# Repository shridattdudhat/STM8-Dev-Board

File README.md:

# STM8-Dev-Board
STM8-Dev-Board with SoC STM8S003F3P6

Ki-CAD Project, to buy this connect me on electroShri@gmail.com

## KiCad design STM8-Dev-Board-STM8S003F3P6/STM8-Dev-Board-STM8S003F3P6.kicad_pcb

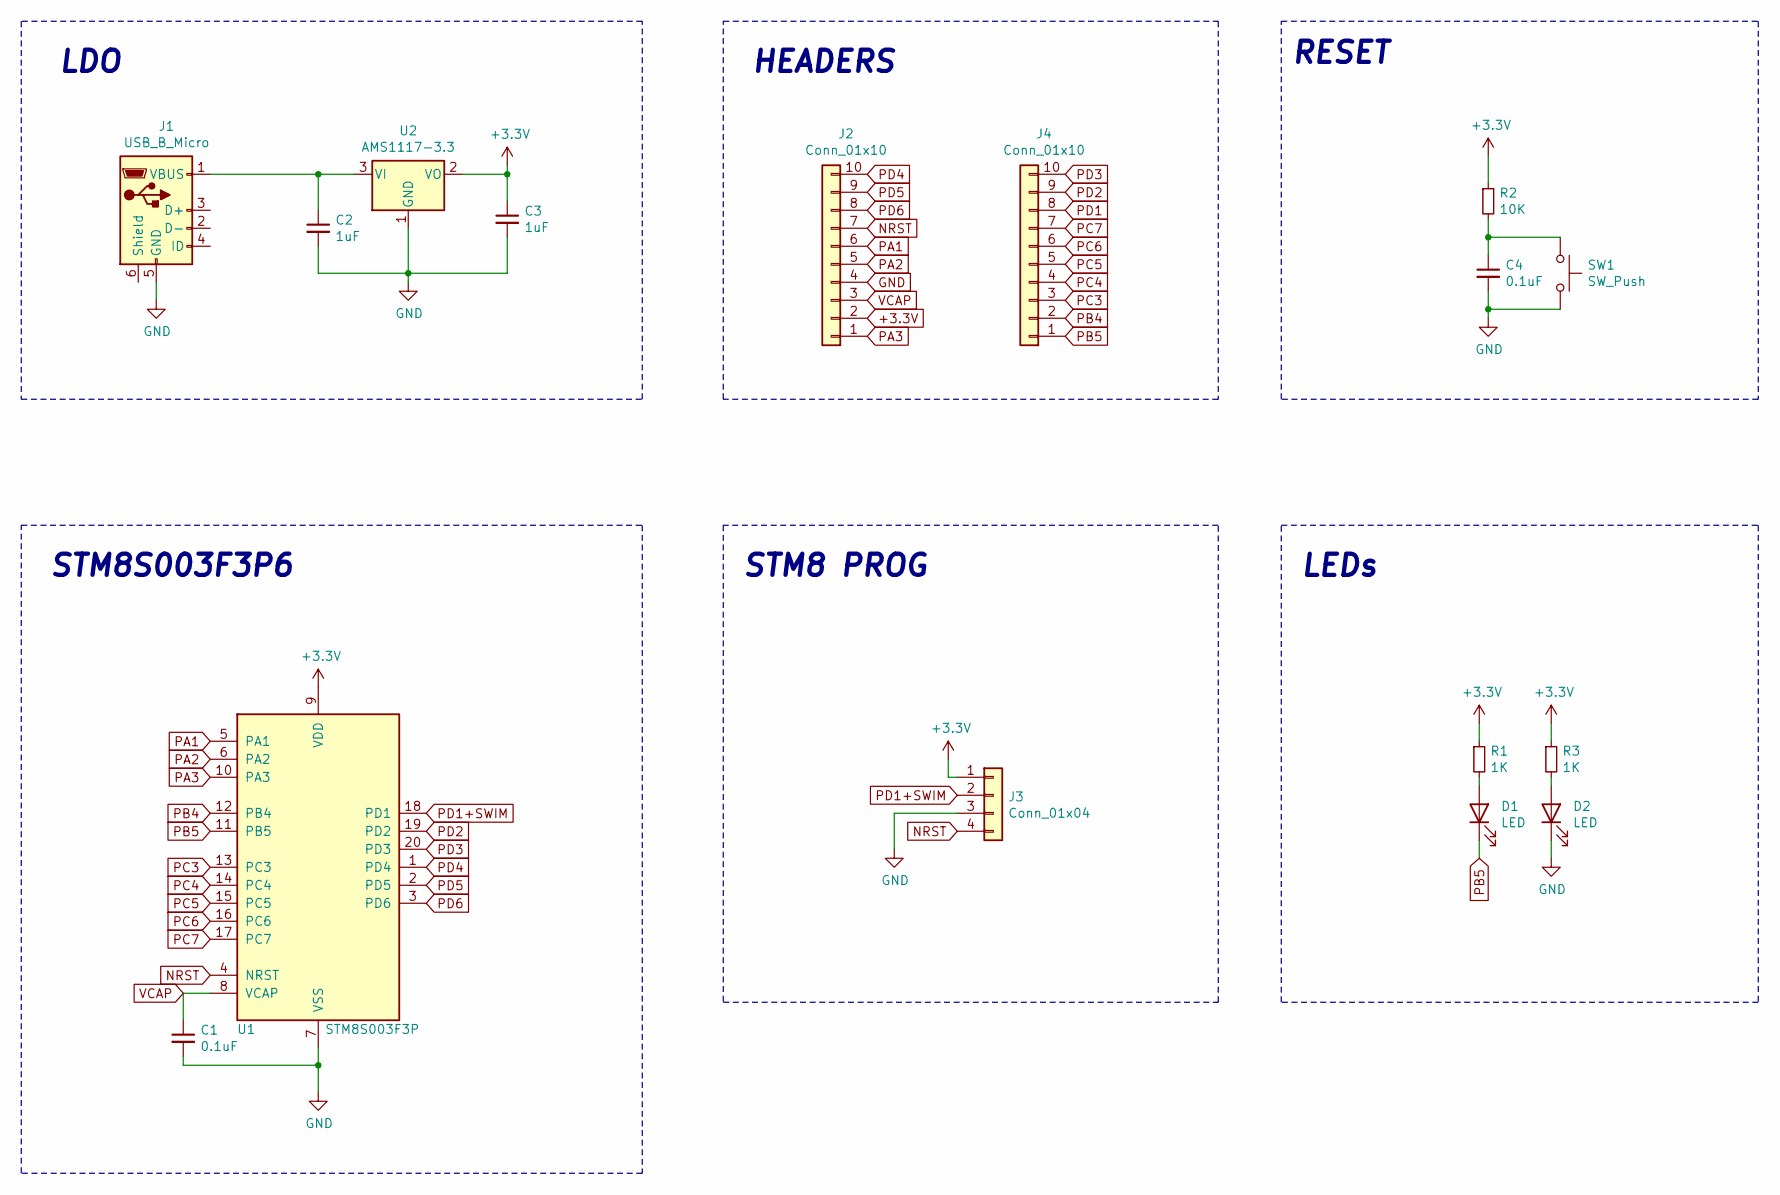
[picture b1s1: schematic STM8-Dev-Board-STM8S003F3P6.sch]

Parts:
C1, C4: 0.1uF; C_0805_2012Metric
C2, C3: 1uF; C_0805_2012Metric
D1, D2: LED; LED_0603_1608Metric
J1: USB_B_Micro; USB_Micro-B_Molex-105017-0001
J2, J4: Conn_01x10; PinHeader_1x10_P2.54mm_Vertical
J3: Conn_01x04; PinHeader_1x04_P2.54mm_Vertical
R1, R3: 1K; R_0805_2012Metric
R2: 10K; R_0805_2012Metric
SW1: SW_Push; SW_SPST_SKQG_WithStem
U1: STM8S003F3P; TSSOP-20_4.4x6.5mm_P0.65mm
U2: AMS1117-3.3; SOT-223-3_TabPin2

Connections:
+3.3V: J2.2
+3V3: C3.1, J3.1, R1.1, R2.1, R3.1, U1.9 (VDD), U2.2 (VO)
GND: C1.2, C2.2, C3.2, C4.2, D2.1 (K), J1.5 (GND), J2.4, J3.3, SW1.2, U1.7 (VSS), U2.1 (GND)
NRST: J2.7, J3.4, U1.4 (NRST)
unnamed: C2.1, J1.1 (VBUS), U2.3 (VI)
unnamed: C4.1, R2.2, SW1.1
unnamed: D1.2 (A), R1.2
unnamed: D2.2 (A), R3.2
PA1: J2.6, U1.5 (PA1)
PA2: J2.5, U1.6 (PA2)
PA3: J2.1, U1.10 (PA3)
PB4: J4.2, U1.12 (PB4)
PB5: D1.1 (K), J4.1, U1.11 (PB5)
PC3: J4.3, U1.13 (PC3)
PC4: J4.4, U1.14 (PC4)
PC5: J4.5, U1.15 (PC5)
PC6: J4.6, U1.16 (PC6)
PC7: J4.7, U1.17 (PC7)
PD1: J4.8
PD1+SWIM: J3.2, U1.18 (PD1)
PD2: J4.9, U1.19 (PD2)
PD3: J4.10, U1.20 (PD3)
PD4: J2.10, U1.1 (PD4)
PD5: J2.9, U1.2 (PD5)
PD6: J2.8, U1.3 (PD6)
VCAP: C1.1, J2.3, U1.8 (VCAP)

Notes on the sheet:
STM8S003F3P6
LDO
HEADERS
RESET
STM8 PROG
LEDs

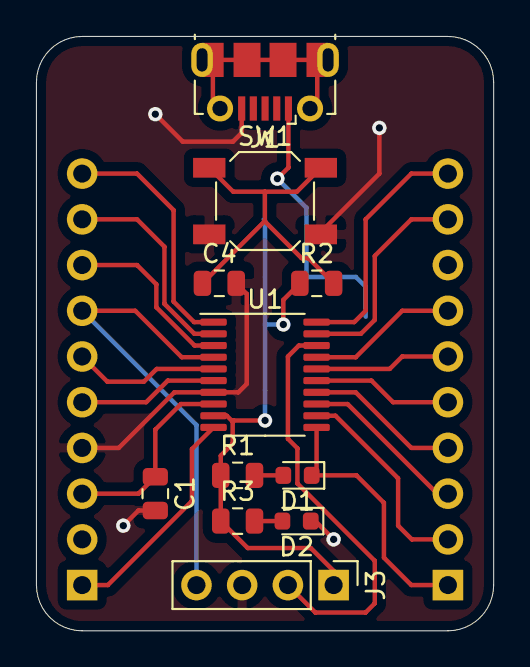
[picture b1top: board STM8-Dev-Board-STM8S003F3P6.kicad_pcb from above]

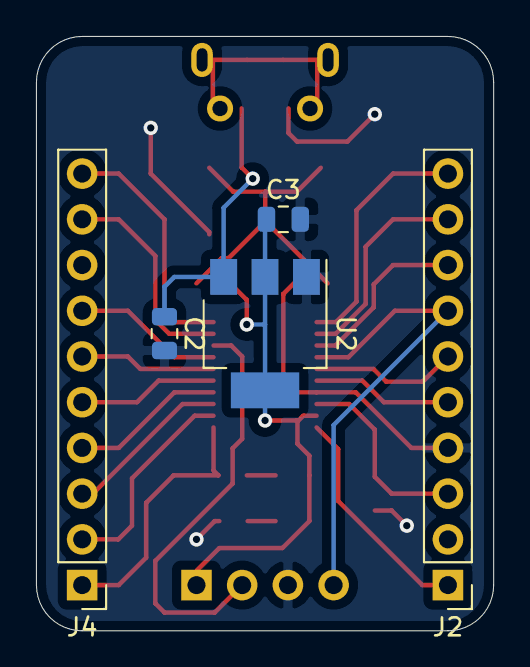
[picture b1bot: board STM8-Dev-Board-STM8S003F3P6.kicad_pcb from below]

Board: 2 copper layers, 25.4 x 33.0 mm, 16 parts (5 on the bottom side), 24 nets.

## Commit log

2020-06-18 Set theme jekyll-theme-cayman
2020-07-17 gerber delete
2020-09-16 Set theme jekyll-theme-hacker
